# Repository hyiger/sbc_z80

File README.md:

THS-80 Model I - a Z80 single board computer on a RC2014 form-factor card

Requires KiCad 5.1.4 or higher

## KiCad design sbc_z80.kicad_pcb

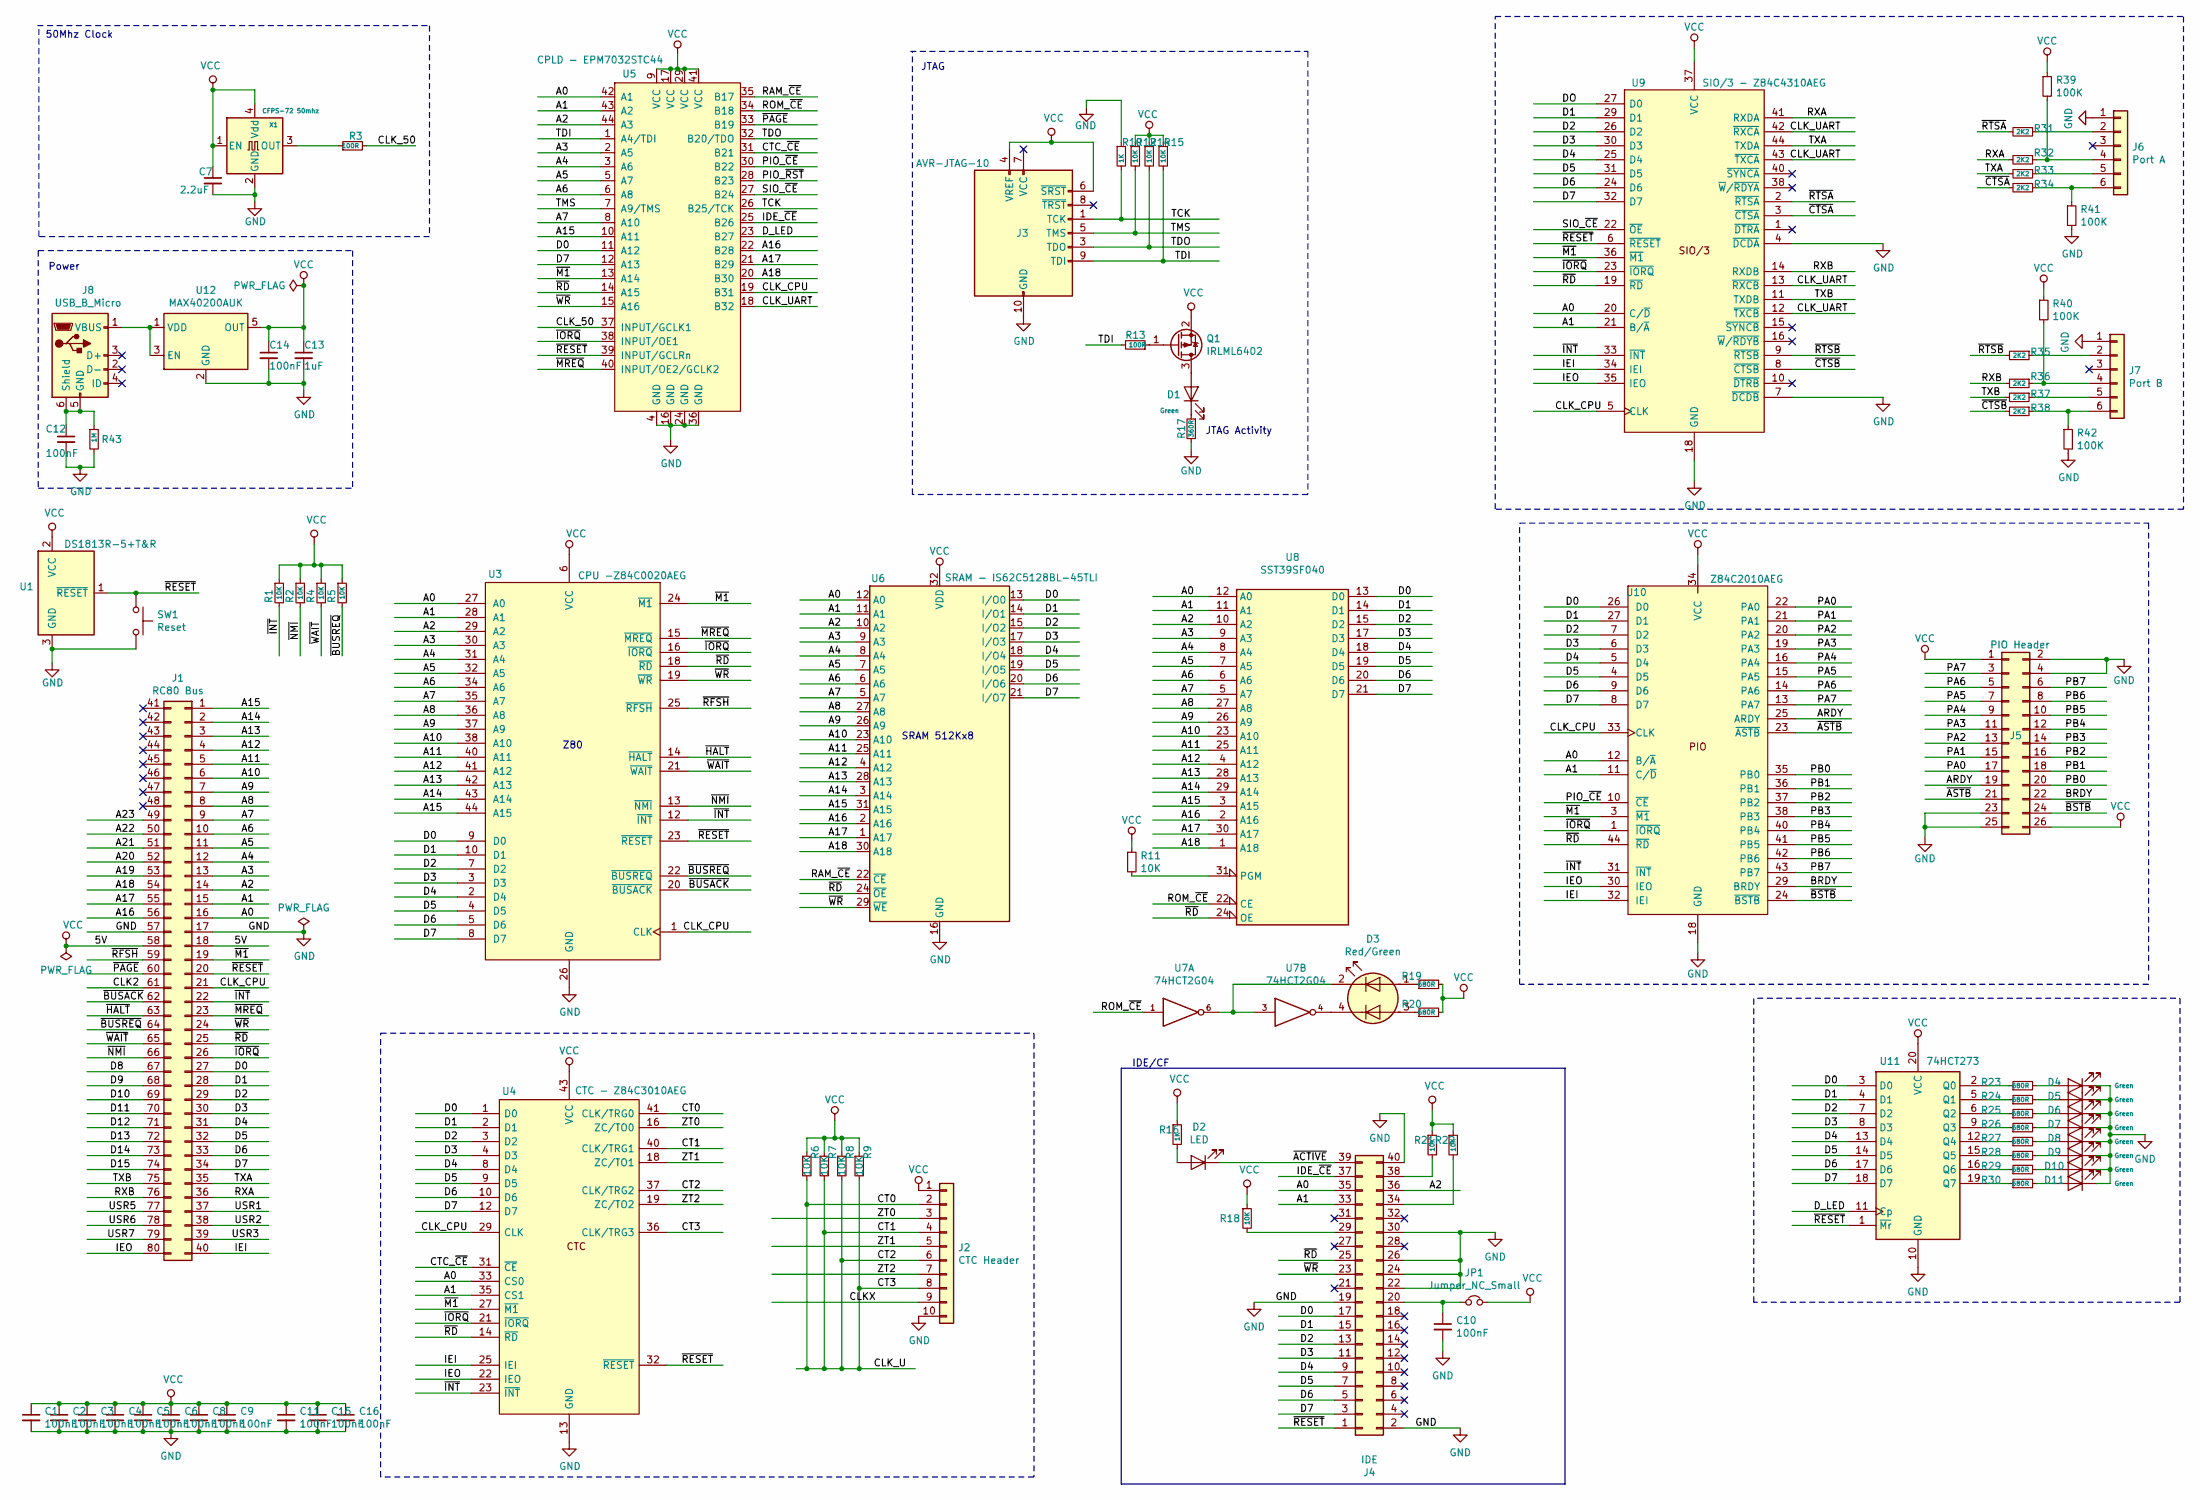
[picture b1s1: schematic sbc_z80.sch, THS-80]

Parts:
C1, C2, C3, C4, C5, C6, C8, C9, C10, C11, C15, C16: 100nF; C_0603_1608Metric_Pad1.05x0.95mm_HandSolder; MPN JMK107B7474KA-T
C7: 2.2uF; C_0603_1608Metric_Pad1.05x0.95mm_HandSolder; MPN JMK107B7474KA-T
C12, C14: 100nF; C_0603_1608Metric_Pad1.05x0.95mm_HandSolder; MPN C0805C105K4RACTU
C13: 1uF; C_0603_1608Metric_Pad1.05x0.95mm_HandSolder; MPN C0805C105K4RACTU
D1, D4, D5, D6, D7, D8, D9, D10, D11: Green; LED_0603_1608Metric_Pad1.05x0.95mm_HandSolder
D2: LED; LED_0603_1608Metric_Pad1.05x0.95mm_HandSolder
D3: Red/Green; LED_2C_0603_1608Metric_Pad1.05x0.95mm_HandSolder
J1: RC80 Bus; PinHeader_2x40_Top_Bottom_P2.54mm_Horizontal
J2: CTC Header; PinHeader_1x10_P2.54mm_Horizontal
J3: AVR-JTAG-10; PinHeader_2x05_P2.54mm_Vertical
J4: IDE; PinHeader_2x20_P2.54mm_Horizontal
J5: PIO Header; PinHeader_2x13_P2.54mm_Horizontal
J6: Port A; PinHeader_1x06_P2.54mm_Horizontal
J7: Port B; PinHeader_1x06_P2.54mm_Horizontal
J8: USB_B_Micro; USB_Micro-B_Molex-105017-0001; MPN 10103594-0001LF
JP1: Jumper_NC_Small; PinHeader_1x02_P2.54mm_Vertical
Q1: IRLML6402; SOT-23
R1, R2, R4, R5, R6, R7, R8, R9, R11, R12, R14, R15, R18, R21, R22: 10K; R_0603_1608Metric_Pad1.05x0.95mm_HandSolder
R3, R13: 100R; R_0603_1608Metric_Pad1.05x0.95mm_HandSolder
R10, R16: 1K; R_0603_1608Metric_Pad1.05x0.95mm_HandSolder
R17: 360R; R_0603_1608Metric_Pad1.05x0.95mm_HandSolder
R19, R20, R23, R24, R25, R26, R27, R28, R29, R30: 680R; R_0603_1608Metric_Pad1.05x0.95mm_HandSolder; MPN RC0603JR-071KL
R31, R32, R33, R34, R35, R36, R37, R38: 2K2; R_0603_1608Metric_Pad1.05x0.95mm_HandSolder
R39, R40, R41, R42: 100K; R_0603_1608Metric_Pad1.05x0.95mm_HandSolder
R43: 1M; R_0603_1608Metric_Pad1.05x0.95mm_HandSolder
SW1: Reset; SW_Push_SPST_NO_Alps_SKRK
U1: DS1813R-5+T&R; SOT-23
U3: CPU -Z84C0020AEG; LQFP-44_10x10mm_P0.8mm; Manufacturer_Part_Number Z84C0010AEG
U4: CTC - Z84C3010AEG; LQFP-44_10x10mm_P0.8mm; Manufacturer_Part_Number Z84C4310AEG
U5: CPLD - EPM7032STC44; TQFP-44_10x10mm_P0.8mm
U6: SRAM - IS62C5128BL-45TLI; TSOP-II-32_21.0x10.2mm_P1.27mm
U7: 74HCT2G04; TSOP-6_1.65x3.05mm_P0.95mm
U8: SST39SF040; PLCC-32_SMD-Socket
U9: SIO/3 - Z84C4310AEG; LQFP-44_10x10mm_P0.8mm; Manufacturer_Part_Number Z84C4310AEG
U10: Z84C2010AEG; LQFP-44_10x10mm_P0.8mm; Manufacturer_Part_Number Z84C2010AEG
U11: 74HCT273; TSSOP-20_4.4x6.5mm_P0.65mm
U12: MAX40200AUK; SOT-23-5_HandSoldering; MPN MAX40200AUK+T; Mouser PN 700-MAX40200AUK+T
X1: CFPS-72 50mhz; Oscillator_SMD_SeikoEpson_SG8002CA-4Pin_7.0x5.0mm_HandSolde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

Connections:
/A0: J1.16, J4.35, U3.27 (A0), U4.33 (CS0), U5.42 (A1), U6.12 (A0), U8.12 (A0), U9.20 (C/~D), U10.12 (B/~A)
/A1: J1.15, J4.33, U3.28 (A1), U4.35 (CS1), U5.43 (A2), U6.11 (A1), U8.11 (A1), U9.21 (B/~A), U10.11 (C/~D)
/A2: J1.14, J4.36, U3.29 (A2), U5.44 (A3), U6.10 (A2), U8.10 (A2)
/A3: J1.13, U3.30 (A3), U5.2 (A5), U6.9 (A3), U8.9 (A3)
/A4: J1.12, U3.31 (A4), U5.3 (A6), U6.8 (A4), U8.8 (A4)
/A5: J1.11, U3.32 (A5), U5.5 (A7), U6.7 (A5), U8.7 (A5)
/A6: J1.10, U3.34 (A6), U5.6 (A8), U6.6 (A6), U8.6 (A6)
/A7: J1.9, U3.35 (A7), U5.8 (A10), U6.5 (A7), U8.5 (A7)
/A8: J1.8, U3.36 (A8), U6.27 (A8), U8.27 (A8)
/A9: J1.7, U3.37 (A9), U6.26 (A9), U8.26 (A9)
/A10: J1.6, U3.38 (A10), U6.23 (A10), U8.23 (A10)
/A11: J1.5, U3.40 (A11), U6.25 (A11), U8.25 (A11)
/A12: J1.4, U3.41 (A12), U6.4 (A12), U8.4 (A12)
/A13: J1.3, U3.42 (A13), U6.28 (A13), U8.28 (A13)
/A14: J1.2, U3.43 (A14), U6.3 (A14), U8.29 (A14)
/A15: J1.1, U3.44 (A15), U5.10 (A11), U6.31 (A15), U8.3 (A15)
/A16: J1.56, U5.22 (B28), U6.2 (A16), U8.2 (A16)
/A17: J1.55, U5.21 (B29), U6.1 (A17), U8.30 (A17)
/A18: J1.54, U5.20 (B30), U6.30 (A18), U8.1 (A18)
/A19: J1.53
/A20: J1.52
/A21: J1.51
/A22: J1.50
/A23: J1.49
/ARDY: J5.19, U10.25 (ARDY)
/BRDY: J5.22, U10.29 (BRDY)
/CLK2: J1.61
/CLKX: J2.9
/CLK_50: R3.2, U5.37 (INPUT/GCLK1)
/CLK_CPU: J1.21, U3.1 (CLK), U4.29 (CLK), U5.19 (B31), U9.5 (CLK), U10.33 (CLK)
/CLK_U: J2.2, J2.4, J2.6, J2.8, R6.2, R7.2, R8.2, R9.2, U4.36 (CLK/TRG3), U4.37 (CLK/TRG2), U4.40 (CLK/TRG1), U4.41 (CLK/TRG0)
/CLK_UART: U5.18 (B32), U9.12 (~TXCB), U9.13 (~RXCB), U9.42 (~RXCA), U9.43 (~TXCA)
/CTC_~CE~: U4.31 (~CE), U5.31 (B21)
/D0: J1.27, J4.17, U3.9 (D0), U4.1 (D0), U5.11 (A12), U6.13 (I/O0), U8.13 (D0), U10.26 (D0), U11.3 (D0)
/D1: J1.28, J4.15, U3.10 (D1), U4.2 (D1), U6.14 (I/O1), U8.14 (D1), U9.29 (D1), U10.27 (D1), U11.4 (D1)
/D2: J1.29, J4.13, U3.7 (D2), U4.3 (D2), U6.15 (I/O2), U8.15 (D2), U9.26 (D2), U10.7 (D2), U11.7 (D2)
/D3: J1.30, J4.11, U3.3 (D3), U4.4 (D3), U6.17 (I/O3), U8.17 (D3), U9.30 (D3), U10.6 (D3), U11.8 (D3)
/D4: J1.31, J4.9, U3.2 (D4), U4.8 (D4), U6.18 (I/O4), U8.18 (D4), U9.25 (D4), U10.5 (D4), U11.13 (D4)
/D5: J1.32, J4.7, U3.4 (D5), U4.9 (D5), U6.19 (I/O5), U8.19 (D5), U9.31 (D5), U10.4 (D5), U11.14 (D5)
/D6: J1.33, J4.5, U3.5 (D6), U4.10 (D6), U6.20 (I/O6), U8.20 (D6), U9.24 (D6), U10.9 (D6), U11.17 (D6)
/D7: J1.34, J4.3, U3.8 (D7), U4.12 (D7), U5.12 (A13), U6.21 (I/O7), U8.21 (D7), U9.32 (D7), U10.8 (D7), U11.18 (D7)
/D8: J1.67
/D9: J1.68
/D10: J1.69
/D11: J1.70
/D12: J1.71
/D13: J1.72
/D14: J1.73
/D15: J1.74
/DO: U9.27 (D0)
/D_LED: U5.23 (B27), U11.11 (Cp)
/IDE_~CE~: J4.37, U5.25 (B26)
/IEI: J1.40, U4.25 (IEI), U9.34 (IEI), U10.32 (IEI)
/IEO: J1.80, U4.22 (IEO), U9.35 (IEO), U10.30 (IEO)
/PA0: J5.17, U10.22 (PA0)
/PA1: J5.15, U10.21 (PA1)
/PA2: J5.13, U10.20 (PA2)
/PA3: J5.11, U10.19 (PA3)
/PA4: J5.9, U10.16 (PA4)
/PA5: J5.7, U10.15 (PA5)
/PA6: J5.5, U10.14 (PA6)
/PA7: J5.3, U10.13 (PA7)
/PB0: J5.20, U10.35 (PB0)
/PB1: J5.18, U10.36 (PB1)
/PB2: J5.16, U10.37 (PB2)
/PB3: J5.14, U10.38 (PB3)
/PB4: J5.12, U10.40 (PB4)
/PB5: J5.10, U10.41 (PB5)
/PB6: J5.8, U10.42 (PB6)
/PB7: J5.6, U10.43 (PB7)
/PIO_~CE~: U5.30 (B22), U10.10 (~CE)
/PIO_~RST~: U5.28 (B23)
/RAM_~CE~: U5.35 (B17), U6.22 (~CE)
/ROM_~CE~: U5.34 (B18), U7.1, U8.22 (CE)
/RXA: J1.36, R32.2, U9.41 (RXDA)
/RXB: J1.76, R36.2, U9.14 (RXDB)
/SIO_~CE~: U5.27 (B24), U9.22 (~OE)
/TCK: J3.1 (TCK), R10.2, U5.26 (B25/TCK)
/TDI: J3.9 (TDI), R13.2, R15.2, U5.1 (A4/TDI)
/TDO: J3.3 (TDO), R14.2, U5.32 (B20/TDO)
/TMS: J3.5 (TMS), R12.2, U5.7 (A9/TMS)
/TXA: J1.35, R33.2, U9.44 (TXDA)
/TXB: J1.75, R37.2, U9.11 (TXDB)
/USR1: J1.37
/USR2: J1.38
/USR3: J1.39
/USR5: J1.77
/USR6: J1.78
/USR7: J1.79
/ZT0: J2.3, U4.16 (ZC/TO0)
/ZT1: J2.5, U4.18 (ZC/TO1)
/ZT2: J2.7, U4.19 (ZC/TO2)
/~ACTIVE: D2.1 (K), J4.39
/~ASTB: J5.21, U10.23 (~ASTB)
/~BSTB: J5.24, U10.24 (~BSTB)
/~BUSACK: J1.62, U3.20 (~BUSACK)
/~BUSREQ: J1.64, R5.2, U3.22 (~BUSREQ)
/~CTSA: R34.2, U9.3 (~CTSA)
/~CTSB: R38.2, U9.8 (~CTSB)
/~HALT: J1.63, U3.14 (~HALT)
/~INT: J1.22, R1.2, U3.12 (~INT), U4.23 (~INT), U9.33 (~INT), U10.31 (~INT)
/~IORQ: J1.26, U3.16 (~IORQ), U4.21 (~IORQ), U5.38 (INPUT/OE1), U9.23 (~IORQ), U10.1 (~IORQ)
/~M1: J1.19, U3.24 (~M1), U4.27 (~M1), U5.13 (A14), U9.36 (~M1), U10.3 (~M1)
/~MREQ: J1.23, U3.15 (~MREQ), U5.40 (INPUT/OE2/GCLK2)
/~NMI: J1.66, R2.2, U3.13 (~NMI)
/~PAGE: J1.60, U5.33 (B19)
/~RD: J1.25, J4.25, U3.18 (~RD), U4.14 (~RD), U5.14 (A15), U6.24 (~OE), U8.24 (OE), U9.19 (~RD), U10.44 (~RD)
/~RESET: J1.20, J4.1, SW1.1, U1.1 (~RESET~), U3.23 (~RESET), U4.32 (~RESET), U5.39 (INPUT/GCLRn), U9.6 (~RESET), U11.1 (~Mr)
/~RFSH: J1.59, U3.25 (~RFSH)
/~RTSA: R31.2, U9.2 (~RTSA)
/~RTSB: R35.2, U9.9 (~RTSB)
/~WAIT: J1.65, R4.2, U3.21 (~WAIT)
/~WR: J1.24, J4.23, U3.19 (~WR), U5.15 (A16), U6.29 (~WE)
GND: C1.2, C2.2, C3.2, C4.2, C5.2, C6.2, C7.2, C8.2, C9.2, C10.2, C11.2, C12.2, C13.2, C14.2, C15.2, C16.2, D4.1 (K), D5.1 (K), D6.1 (K), D7.1 (K), D8.1 (K), D9.1 (K), D10.1 (K), D11.1 (K), J1.17, J1.57, J2.10, J3.2 (GND), J3.10 (GND), J4.2, J4.19, J4.22, J4.24, J4.26, J4.30, J4.40, J5.2, J5.4, J5.23, J5.25, J6.1, J7.1, R10.1, R17.2, R41.2, R42.2, R43.2, SW1.2, U1.3 (GND), U3.26 (GND), U4.13 (GND), U5.4 (GND), U5.16 (GND), U5.24 (GND), U5.36 (GND), U6.16 (GND), U7.2 (GND), U8.16 (GND), U9.4 (~DCDA), U9.7 (~DCDB), U9.18 (GND), U10.18 (GND), U11.10 (GND), U12.2 (GND), X1.2 (GND)
unnamed: C10.1, J4.20, JP1.1
unnamed: C12.1, J8.5 (GND), J8.6 (Shield), R43.1
unnamed: D1.1 (K), R17.1
unnamed: D1.2 (A), Q1.3 (D)
unnamed: D2.2 (A), R16.2
unnamed: D3.1 (A1), R19.1
unnamed: D3.2 (K1), U7.3, U7.6
unnamed: D3.3 (A2), R20.1
unnamed: D3.4 (K2), U7.4
unnamed: D4.2 (A), R23.2
unnamed: D5.2 (A), R24.2
unnamed: D6.2 (A), R25.2
unnamed: D7.2 (A), R26.2
unnamed: D8.2 (A), R27.2
unnamed: D9.2 (A), R28.2
unnamed: D10.2 (A), R29.2
unnamed: D11.2 (A), R30.2
unnamed: J4.29, R18.2
unnamed: J4.34, R22.2
unnamed: J4.38, R21.2
unnamed: J6.2, R31.1
unnamed: J6.4, R32.1, R39.2
unnamed: J6.5, R33.1
unnamed: J6.6, R34.1, R41.1
unnamed: J7.2, R35.1
unnamed: J7.4, R36.1, R40.2
unnamed: J7.5, R37.1
unnamed: J7.6, R38.1, R42.1
unnamed: J8.1 (VBUS), U12.1 (VDD), U12.3 (EN)
unnamed: Q1.1 (G), R13.1
unnamed: R3.1, X1.3 (OUT)
unnamed: R11.2, U8.31 (PGM)
unnamed: R23.1, U11.2 (Q0)
unnamed: R24.1, U11.5 (Q1)
unnamed: R25.1, U11.6 (Q2)
unnamed: R26.1, U11.9 (Q3)
unnamed: R27.1, U11.12 (Q4)
unnamed: R28.1, U11.15 (Q5)
unnamed: R29.1, U11.16 (Q6)
unnamed: R30.1, U11.19 (Q7)
VCC: C1.1, C2.1, C3.1, C4.1, C5.1, C6.1, C7.1, C8.1, C9.1, C11.1, C13.1, C14.1, C15.1, C16.1, J1.18, J1.58, J2.1, J3.4 (VREF), J3.6 (~SRST), J5.1, J5.26, JP1.2, Q1.2 (S), R1.1, R2.1, R4.1, R5.1, R6.1, R7.1, R8.1, R9.1, R11.1, R12.1, R14.1, R15.1, R16.1, R18.1, R19.2, R20.2, R21.1, R22.1, R39.1, R40.1, U1.2 (VCC), U3.6 (VCC), U4.43 (VCC), U5.9 (VCC), U5.17 (VCC), U5.29 (VCC), U5.41 (VCC), U6.32 (VDD), U7.5 (VCC), U8.32 (VCC), U9.37 (VCC), U10.34 (VCC), U11.20 (VCC), U12.5 (OUT), X1.1 (EN), X1.4 (Vdd)

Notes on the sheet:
SRAM 512Kx8
Z80
50Mhz Clock
JTAG
JTAG Activity
IDE/CF
Power

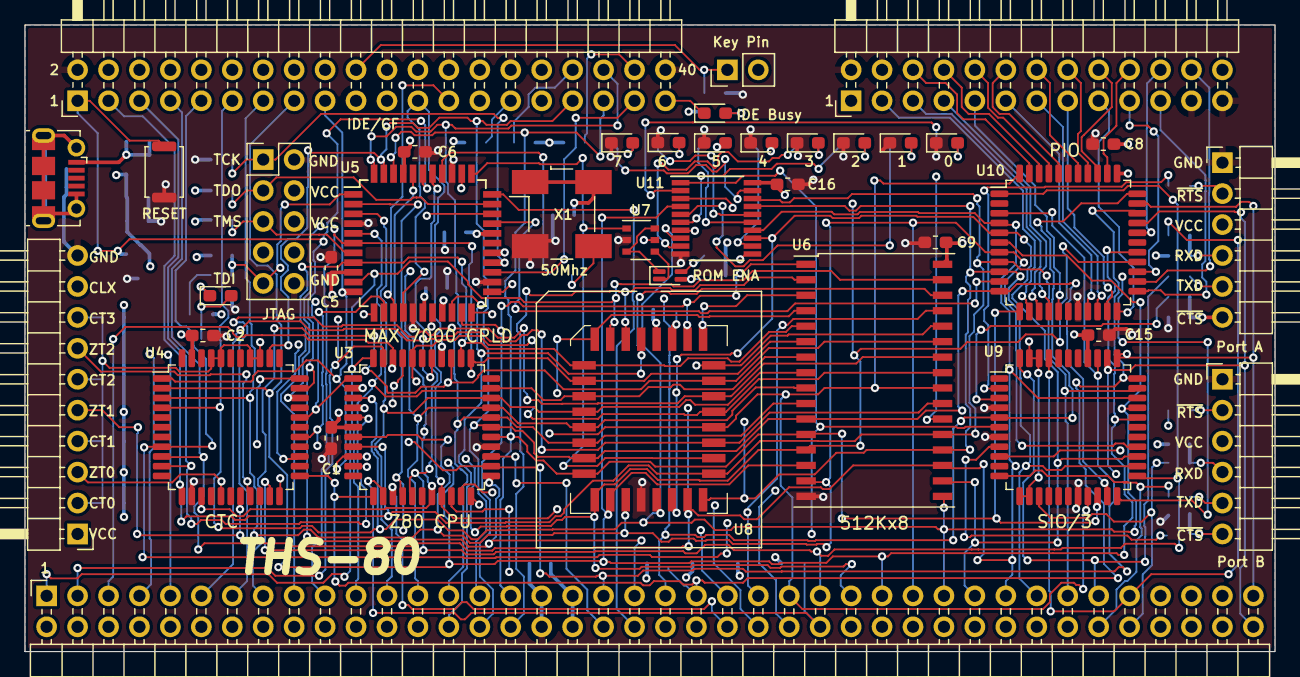
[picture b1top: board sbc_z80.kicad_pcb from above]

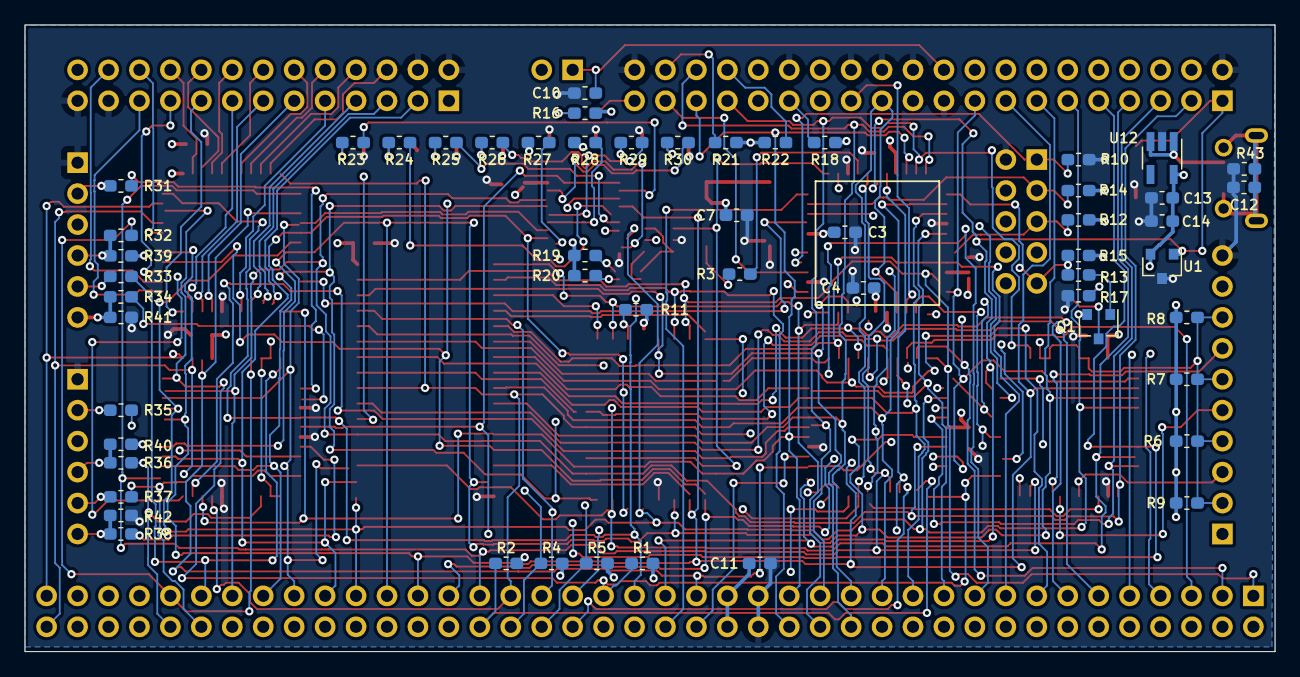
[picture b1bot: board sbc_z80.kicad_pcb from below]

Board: 4 copper layers, 102.6 x 51.4 mm, 93 parts (54 on the bottom side), 132 nets.

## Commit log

2019-06-24 initial revision
2019-06-25 added 3V3 section for clock generator
2019-06-26 larger sheet, connected more pins
2019-06-27 started routing
2019-06-28 fixed up ce signals
2019-06-28 removed empty submodule
2019-07-01 reordered resistors
2019-07-05 changed part layouts
2019-07-08 cleanup
2019-07-11 added display, config switch
2019-07-12 fixed NC pins
2019-07-15 code for max7000 glue logic
2019-07-16 add i2c master
2019-07-31 cleaned up display sheet
2019-07-31 fixed pins
2019-08-06 changed part layout, removed switch
2019-08-07 added USB power, fixed layout
2019-08-07 routing
2019-08-08 address lines routed
2019-08-08 data lines on inner layers
2019-08-09 more routing
2019-08-09 checkpoint
2019-08-12 routed...
2019-08-13 passed drc
2019-08-13 fixed layout, added labels
2019-09-01 update zone-fills to latest nightly
